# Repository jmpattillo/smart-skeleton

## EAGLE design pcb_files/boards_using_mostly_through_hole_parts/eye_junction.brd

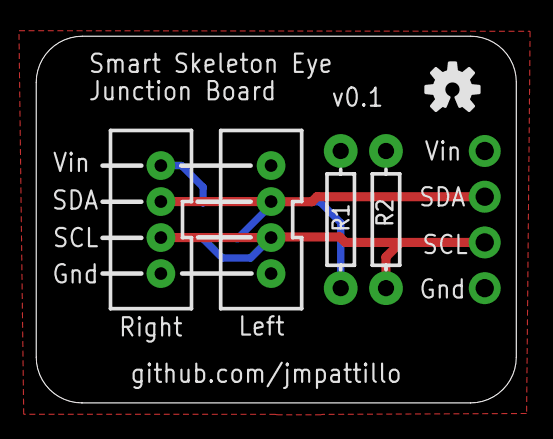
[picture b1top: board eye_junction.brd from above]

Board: 2 copper layers, 26.7 x 20.4 mm, 10 parts (1 on the bottom side), 4 nets.

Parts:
J1, J2: JST-4-PTH-VERT
JP2, JP3, JP4, JP5: 1X01-CLEANBIG
LOGO1: OSHW-LOGOS; OSHW-LOGO-S
R1, R2: AXIAL-0.3
U$2: TVS_ARRAY_CD143A; SOT-143

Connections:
GND: J1.1, J2.1, JP3.1, U$2.GND
SCL: J1.2, J2.2, JP4.1, R2.P$1, U$2.IO2
SDA: J1.3, J2.3, JP2.1, R1.P$1, U$2.IO1
VCC: J1.4, J2.4, JP5.1, R1.P$2, R2.P$2, U$2.VCC

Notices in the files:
parts and their libraries:
SparkFun-Passives: Licensing: Creative Commons ShareAlike 4.0 International - https://creativecommons.org/licenses/by-sa/4.0
